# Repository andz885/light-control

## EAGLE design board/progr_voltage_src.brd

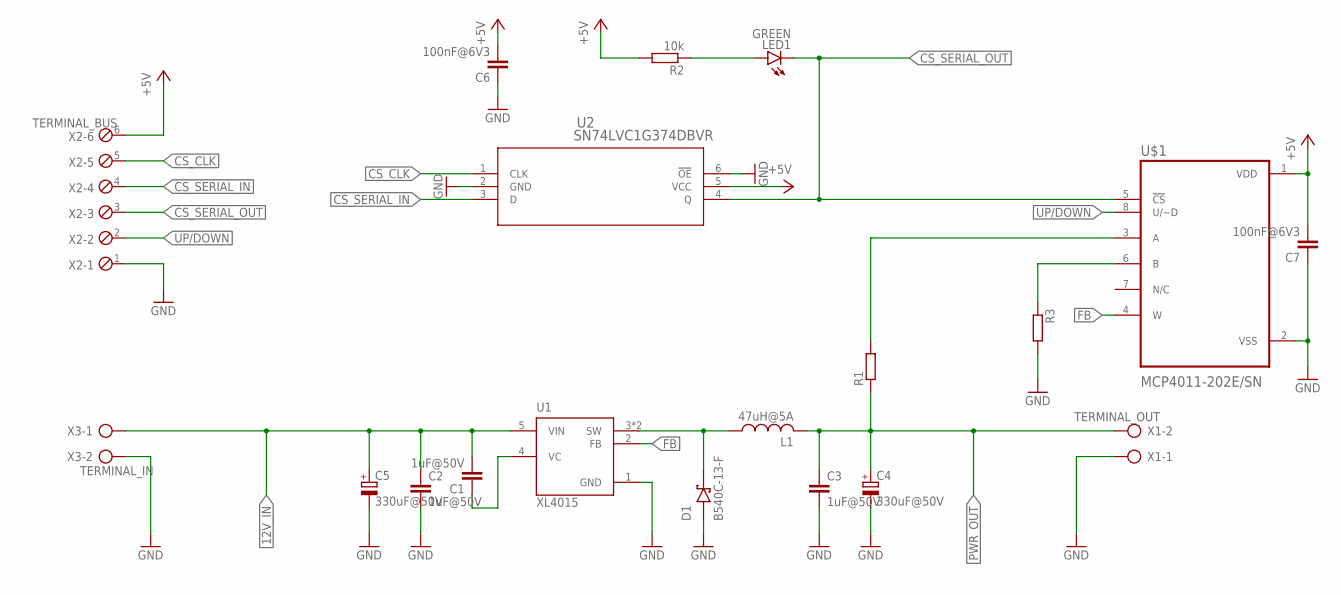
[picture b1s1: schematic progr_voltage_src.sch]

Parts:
C1, C2, C3: 1uF@50V; C0603
C4, C5: 330uF@50V; UD-6,3X7,7_NICHICON
C6, C7: 100nF@6V3; C0603
D1: B540C-13-F; DIOM6959X245N
L1: 47uH@5A; SMD_INDUCTOR_13X12X6
LED1: GREEN; LED3MM
R1, R3: R-EU_R0603; R0603
R2: 10k; R0603
U1: XL4015; CONV_XL4015
U2: SN74LVC1G374DBVR; DBV6
U$1: MCP4011-202E/SN; SOIC127P600X175-8N
X1: TERMINAL_OUT; AK500/2
X2: TERMINAL_BUS; 6POL254
X3: TERMINAL_IN; AK500/2

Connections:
12V_IN: C1.2, C2.1, C5.+, U1.5 (VIN), X3.1
+5V: C6.2, C7.2, R2.2, U2.5 (VCC), U$1.1 (VDD), X2.6
CS_CLK: U2.1 (CLK), X2.5
CS_SERIAL_IN: U2.3 (D), X2.4
CS_SERIAL_OUT: LED1.K (C), U2.4 (Q), U$1.5 (!CS), X2.3
FB: U1.2 (FB), U$1.4 (W)
GND: C2.2, C3.2, C4.-, C5.-, C6.1, C7.1, D1.A, R3.2, U1.1 (GND), U2.2 (GND), U2.6 (!OE), U$1.2 (VSS), X1.1, X2.1, X3.2
unnamed: D1.C (K), L1.P$1 (1), U1.3 (SW), U1.3.1 (SW)
unnamed: LED1.A, R2.1
unnamed: C1.1, U1.4 (VC)
unnamed: R3.1, U$1.6 (B)
unnamed: R1.2, U$1.3 (A)
PWR_OUT: C3.1, C4.+, L1.P$2 (2), R1.1, X1.2
UP/DOWN: U$1.8 (U/~D), X2.2

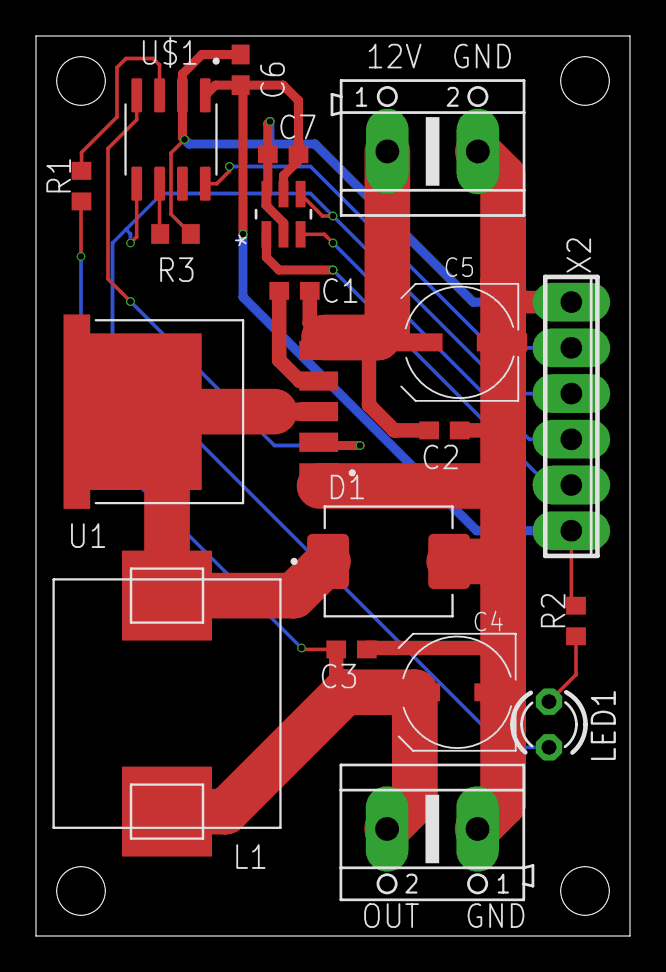
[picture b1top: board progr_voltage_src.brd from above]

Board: 2 copper layers, 33.0 x 50.0 mm, 19 parts (0 on the bottom side), 14 nets.

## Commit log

2024-03-17 removed arduino json

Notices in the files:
parts and their libraries:
COPYRIGHT: Copyright (C) 2023 Ultra Librarian. All rights reserved.
